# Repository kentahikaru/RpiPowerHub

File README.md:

# RpiPowerBoard

# How To use
 |  | 
--- | --- | ---

# Assembly
 | 
--- | ---

# Design
## Schematics

## Board
 | 
--- | ---

# Outcome
 | 
--- | ---

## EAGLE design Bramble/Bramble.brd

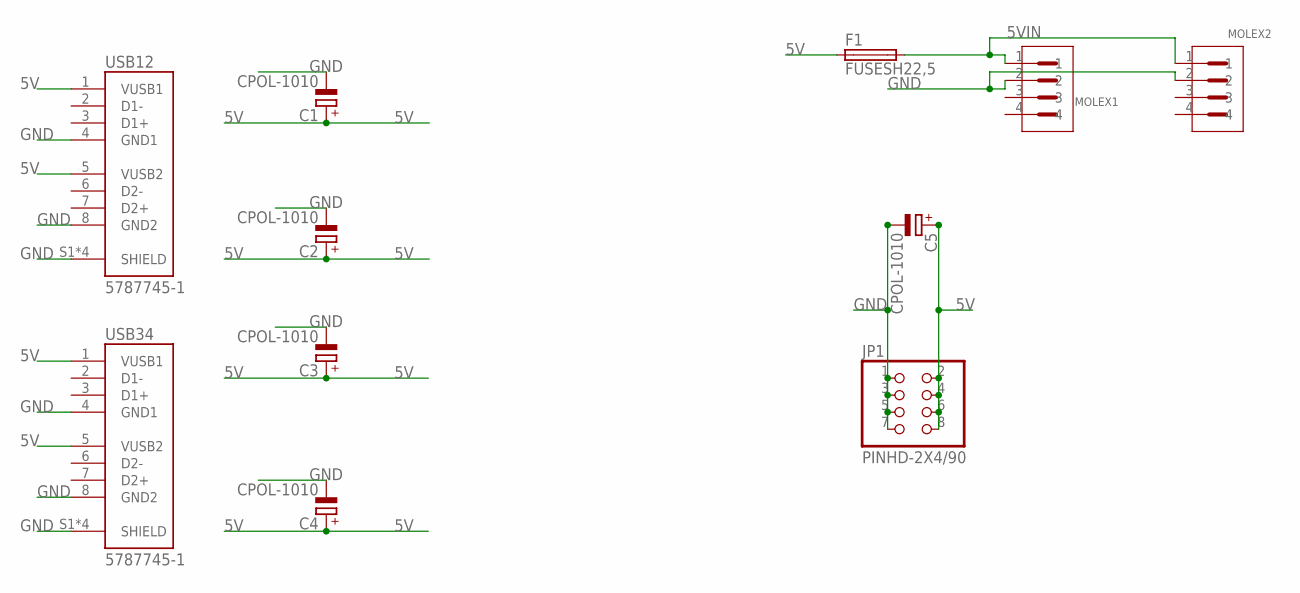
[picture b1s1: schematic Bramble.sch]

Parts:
C1, C2, C3, C4, C5: CPOL-1010; 153CLV-1010
F1: FUSESH22,5; SH22,5
JP1: PINHD-2X4/90; 2X04/90
MOLEX1, MOLEX2: 15244441; MOLEX_15244441
USB12, USB34: 5787745-1; TE_5787745-1

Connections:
5V: C1.+, C2.+, C3.+, C4.+, C5.+, F1.1, JP1.2, JP1.4, JP1.6, JP1.8, USB12.1 (VUSB1), USB12.5 (VUSB2), USB34.1 (VUSB1), USB34.5 (VUSB2)
5VIN: F1.2, MOLEX1.1, MOLEX2.1
GND: C1.-, C2.-, C3.-, C4.-, C5.-, JP1.1, JP1.3, JP1.5, JP1.7, MOLEX1.2, MOLEX2.2, USB12.4 (GND1), USB12.8 (GND2), USB12.S1 (SHIELD), USB12.S2 (SHIELD), USB12.S3 (SHIELD), USB12.S4 (SHIELD), USB34.4 (GND1), USB34.8 (GND2), USB34.S1 (SHIELD), USB34.S2 (SHIELD), USB34.S3 (SHIELD), USB34.S4 (SHIELD)

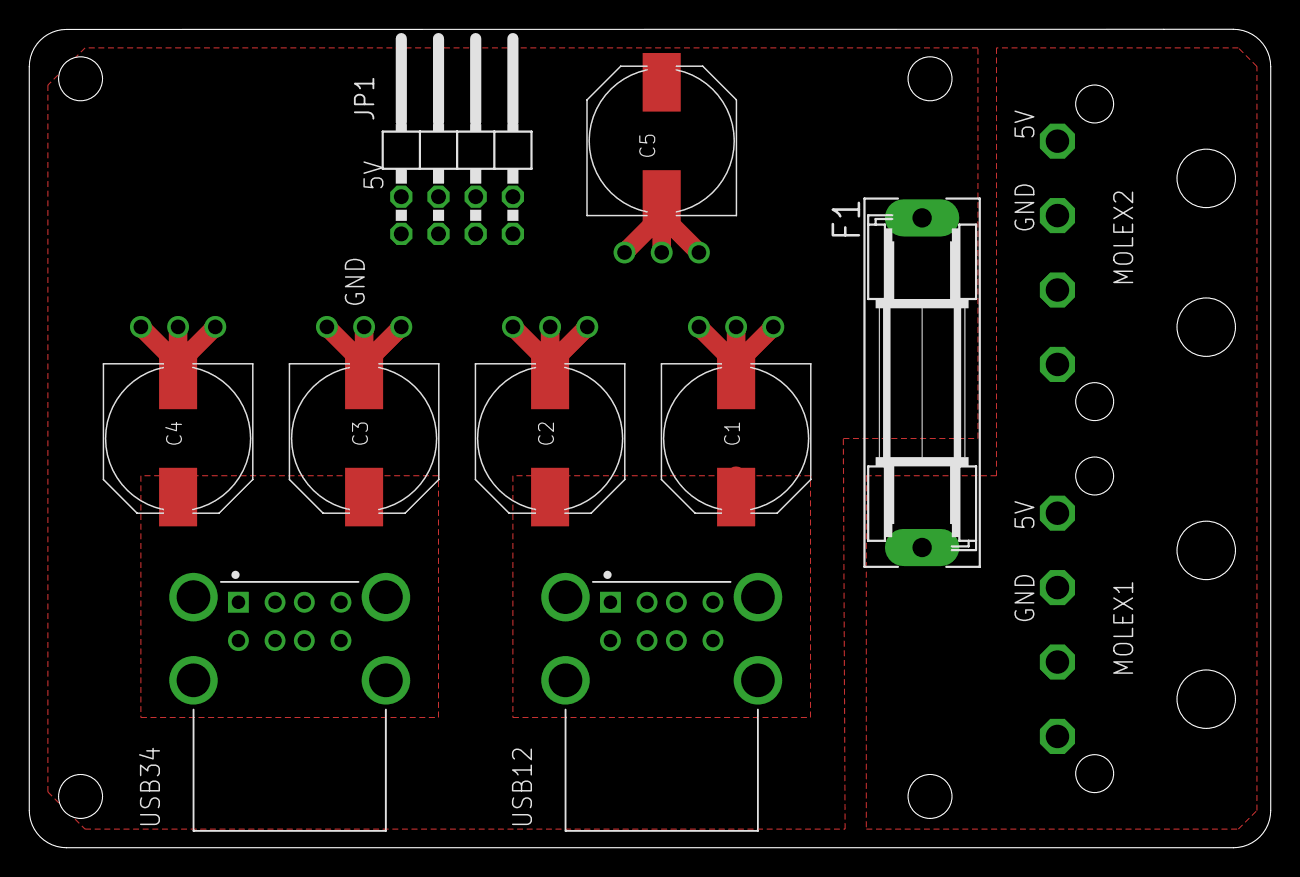
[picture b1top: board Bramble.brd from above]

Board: 2 copper layers, 84.8 x 55.9 mm, 11 parts (0 on the bottom side), 3 nets.

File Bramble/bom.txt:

Partlist exported from /mnt/data/Development/eagle/Bramble/Bramble/Bramble.sch at 7/19/25 10:58 AM

Part   Value        Device       Package        Description                                                                                    AVAILABILITY CATEGORY  COMMENT   DESCRIPTION                                                                      EU_ROHS_COMPLIANCE MANUFACTURER MF              MP         MPN OC_FARNELL OC_NEWARK OPERATING_TEMP PACKAGE PART_STATUS POPULARITY PRICE PURCHASE-URL                                               ROHS_COMPLIANT SERIES SUB-CATEGORY THERMALLOSS TYPE
C1     CPOL-1010    CPOL-1010    153CLV-1010                                                                                                                                                                                                                                                                                                                                                                                                                                                                           
C2     CPOL-1010    CPOL-1010    153CLV-1010                                                                                                                                                                                                                                                                                                                                                                                                                                                                           
C3     CPOL-1010    CPOL-1010    153CLV-1010                                                                                                                                                                                                                                                                                                                                                                                                                                                                           
C4     CPOL-1010    CPOL-1010    153CLV-1010                                                                                                                                                                                                                                                                                                                                                                                                                                                                           
C5     CPOL-1010    CPOL-1010    153CLV-1010                                                                                                                                                                                                                                                                                                                                                                                                                                                                           
F1     FUSESH22,5   FUSESH22,5   SH22,5         Fuse                                                                                                                                                                                                                                                                            unknown    unknown                                      8                                                                                                                              
JP1    PINHD-2X4/90 PINHD-2X4/90 2X04/90        PIN HEADER                                                                                                  CONNECTOR                                                                                                                                                                                                                                                                                                                     PIN-HEADER                   
MOLEX1 15244441     15244441     MOLEX_15244441 Conn Disk Drive Power HDR 4 POS 5.08mm Solder RA Thru-Hole 4 Terminal 1 Port Tray Check prices Bad                               Connector Header Through Hole, Right Angle 4 position 0.200 (5.08mm)                                            Molex           15-24-4441                                         None                           None                                                                                                                
MOLEX2 15244441     15244441     MOLEX_15244441 Conn Disk Drive Power HDR 4 POS 5.08mm Solder RA Thru-Hole 4 Terminal 1 Port Tray Check prices Bad                               Connector Header Through Hole, Right Angle 4 position 0.200 (5.08mm)                                            Molex           15-24-4441                                         None                           None                                                                                                                
USB12  5787745-1    5787745-1    TE_5787745-1   Conn USB 2.0 Type A RCP/RCP 4/4 POS Solder RA Thru-Hole 8 Terminal 2 Port Tray Check prices    Good                   5787745-1  Conn USB 2.0 Type A RCP/RCP 4/4 POS Solder RA Thru-Hole 8 Terminal 2 Port Tray  Compliant                       TE Connectivity 5787745-1                                          None                           None  https://pricing.snapeda.com/search/part/5787745-1/?ref=eda                                                    
USB34  5787745-1    5787745-1    TE_5787745-1   Conn USB 2.0 Type A RCP/RCP 4/4 POS Solder RA Thru-Hole 8 Terminal 2 Port Tray Check prices    Good                   5787745-1  Conn USB 2.0 Type A RCP/RCP 4/4 POS Solder RA Thru-Hole 8 Terminal 2 Port Tray  Compliant                       TE Connectivity 5787745-1                                          None                           None  https://pricing.snapeda.com/search/part/5787745-1/?ref=eda

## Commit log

2020-09-05 Initial commit, added .gitignore
2020-09-05 Added labels
2020-09-05 ERC errors
2020-10-12 Upgrades
2020-10-12 Capacitors among USB connectors
2020-10-12 Rotated PWR IN connector
2020-10-12 Added capacitors for fans
2020-10-14 Reduction to 4 ports and SMD parts
2020-10-14 Tweaked labels
2020-10-14 Tweaking
2020-10-15 Design fix
2020-10-17 Updated laels
2020-10-17 2x 2 port usb
2020-10-17 joined 1 and 2 aaand 3 and 4
2020-10-17 Moved capacitor
2020-10-17 Updated ferite bead value
2020-10-17 Library reference
2020-10-17 Tweaked parts position
2020-10-18 Turned on bottom layer
2020-10-18 Altered ferite beed position
2020-10-19 Updated fuse holder
2020-10-23 Parts position tweaks
2020-10-23 Added gerber generator cam and bottom silkscreen description
2020-12-10 Added Bill of materials
2020-12-10 Added images, written Readme.md
2020-12-13 Added How to use images
2021-01-07 Added assembly pictures
2025-07-19 updated board
